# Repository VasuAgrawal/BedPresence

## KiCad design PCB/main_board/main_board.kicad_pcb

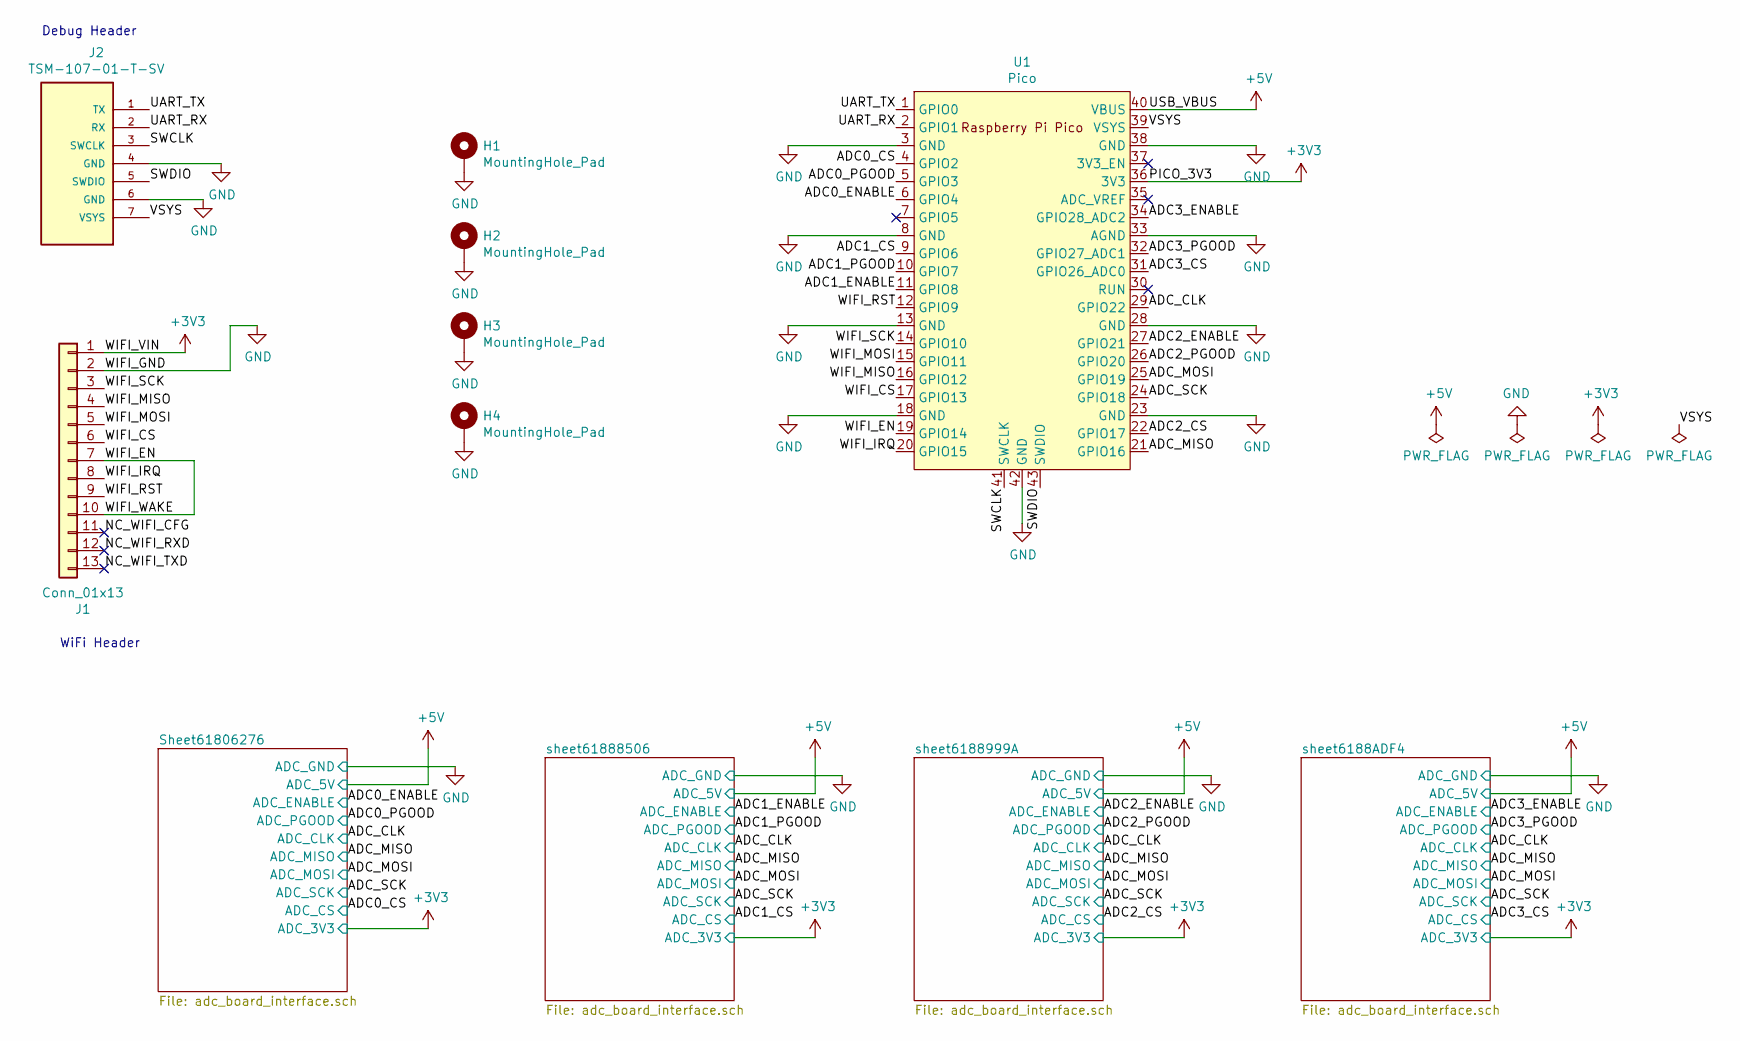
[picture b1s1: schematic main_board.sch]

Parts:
H1, H2, H3, H4: MountingHole_Pad; MountingHole_3.2mm_M3_Pad_Via
J1: Conn_01x13; PinHeader_1x13_P2.54mm_Vertical_SMD_Pin1Left_with_holes
J2: TSM-107-01-T-SV; SAMTEC_TSM-107-01-T-SV
U1: Pico; RPi_Pico_SMD

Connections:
+3V3: J1.1, U1.36 (3V3); also elsewhere on the board
+5V: U1.40 (VBUS); also elsewhere on the board
/ADC0_CS: U1.4 (GPIO2); also elsewhere on the board
/ADC0_ENABLE: U1.6 (GPIO4); also elsewhere on the board
/ADC0_PGOOD: U1.5 (GPIO3); also elsewhere on the board
/ADC1_CS: U1.9 (GPIO6); also elsewhere on the board
/ADC1_ENABLE: U1.11 (GPIO8); also elsewhere on the board
/ADC1_PGOOD: U1.10 (GPIO7); also elsewhere on the board
/ADC2_CS: U1.22 (GPIO17); also elsewhere on the board
/ADC2_ENABLE: U1.27 (GPIO21); also elsewhere on the board
/ADC2_PGOOD: U1.26 (GPIO20); also elsewhere on the board
/ADC3_CS: U1.31 (GPIO26_ADC0); also elsewhere on the board
/ADC3_ENABLE: U1.34 (GPIO28_ADC2); also elsewhere on the board
/ADC3_PGOOD: U1.32 (GPIO27_ADC1); also elsewhere on the board
/ADC_CLK: U1.29 (GPIO22); also elsewhere on the board
/ADC_MISO: U1.21 (GPIO16); also elsewhere on the board
/ADC_MOSI: U1.25 (GPIO19); also elsewhere on the board
/ADC_SCK: U1.24 (GPIO18); also elsewhere on the board
/NC_WIFI_CFG: J1.11
/NC_WIFI_RXD: J1.12
/NC_WIFI_TXD: J1.13
/SWCLK: J2.3 (SWCLK), U1.41 (SWCLK)
/SWDIO: J2.5 (SWDIO), U1.43 (SWDIO)
/UART_RX: J2.2 (RX), U1.2 (GPIO1)
/UART_TX: J2.1 (TX), U1.1 (GPIO0)
/VSYS: J2.7 (VSYS), U1.39 (VSYS)
/WIFI_CS: J1.6, U1.17 (GPIO13)
/WIFI_EN: J1.7, J1.10, U1.19 (GPIO14)
/WIFI_IRQ: J1.8, U1.20 (GPIO15)
/WIFI_MISO: J1.4, U1.16 (GPIO12)
/WIFI_MOSI: J1.5, U1.15 (GPIO11)
/WIFI_RST: J1.9, U1.12 (GPIO9)
/WIFI_SCK: J1.3, U1.14 (GPIO10)
GND: H1.1, H2.1, H3.1, H4.1, J1.2, J2.4 (GND), J2.6 (GND), U1.3 (GND), U1.8 (GND), U1.13 (GND), U1.18 (GND), U1.23 (GND), U1.28 (GND), U1.33 (AGND), U1.38 (GND), U1.42 (GND); also elsewhere on the board

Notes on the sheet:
WiFi Header
Debug Header

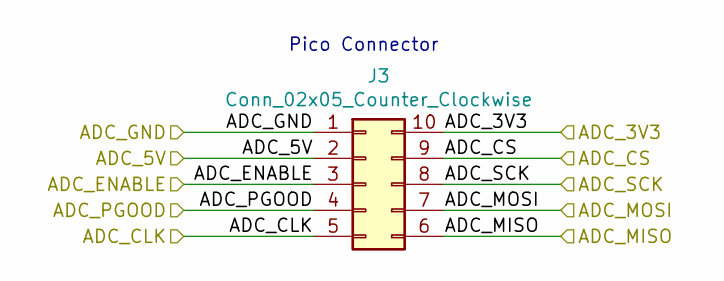
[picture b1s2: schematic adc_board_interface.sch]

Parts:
J3: Conn_02x05_Counter_Clockwise; PinHeader_2x05_P2.54mm_Vertical_SMD

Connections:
+3V3: J3.10; also elsewhere on the board
+5V: J3.2; also elsewhere on the board
/ADC0_CS: J3.9; also elsewhere on the board
/ADC0_ENABLE: J3.3; also elsewhere on the board
/ADC0_PGOOD: J3.4; also elsewhere on the board
/ADC_CLK: J3.5; also elsewhere on the board
/ADC_MISO: J3.6; also elsewhere on the board
/ADC_MOSI: J3.7; also elsewhere on the board
/ADC_SCK: J3.8; also elsewhere on the board
GND: J3.1; also elsewhere on the board

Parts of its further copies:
J4, J5, J6: Conn_02x05_Counter_Clockwise; PinHeader_2x05_P2.54mm_Vertical_SMD

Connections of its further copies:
+3V3: J4.10, J5.10, J6.10; also elsewhere on the board
+5V: J4.2, J5.2, J6.2; also elsewhere on the board
/ADC1_CS: J4.9; also elsewhere on the board
/ADC1_ENABLE: J4.3; also elsewhere on the board
/ADC1_PGOOD: J4.4; also elsewhere on the board
/ADC2_CS: J5.9; also elsewhere on the board
/ADC2_ENABLE: J5.3; also elsewhere on the board
/ADC2_PGOOD: J5.4; also elsewhere on the board
/ADC3_CS: J6.9; also elsewhere on the board
/ADC3_ENABLE: J6.3; also elsewhere on the board
/ADC3_PGOOD: J6.4; also elsewhere on the board
/ADC_CLK: J4.5, J5.5, J6.5; also elsewhere on the board
/ADC_MISO: J4.6, J5.6, J6.6; also elsewhere on the board
/ADC_MOSI: J4.7, J5.7, J6.7; also elsewhere on the board
/ADC_SCK: J4.8, J5.8, J6.8; also elsewhere on the board
GND: J4.1, J5.1, J6.1; also elsewhere on the board

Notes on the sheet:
Pico Connector

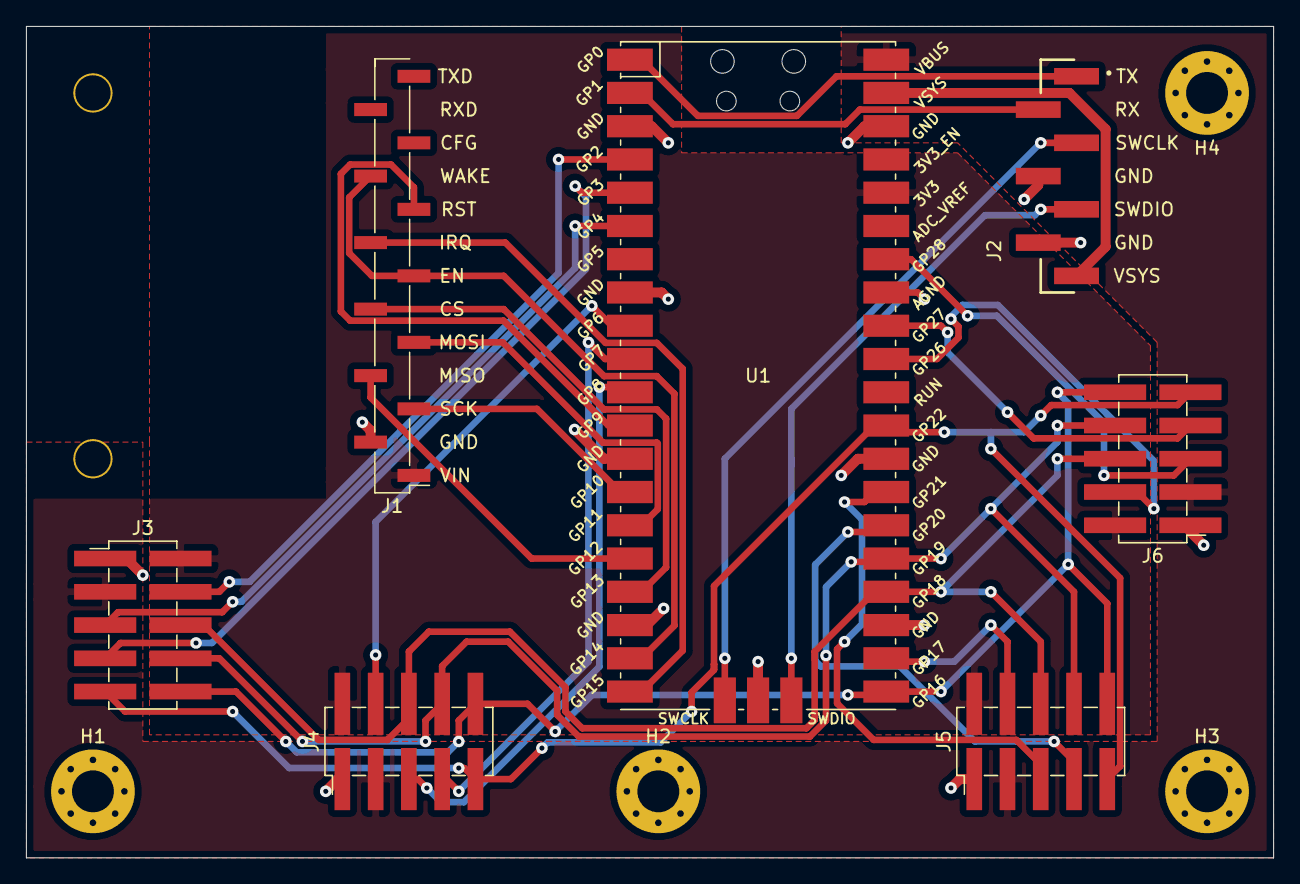
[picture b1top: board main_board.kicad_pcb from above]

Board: 2 copper layers, 95.2 x 63.5 mm, 11 parts (0 on the bottom side), 31 nets.

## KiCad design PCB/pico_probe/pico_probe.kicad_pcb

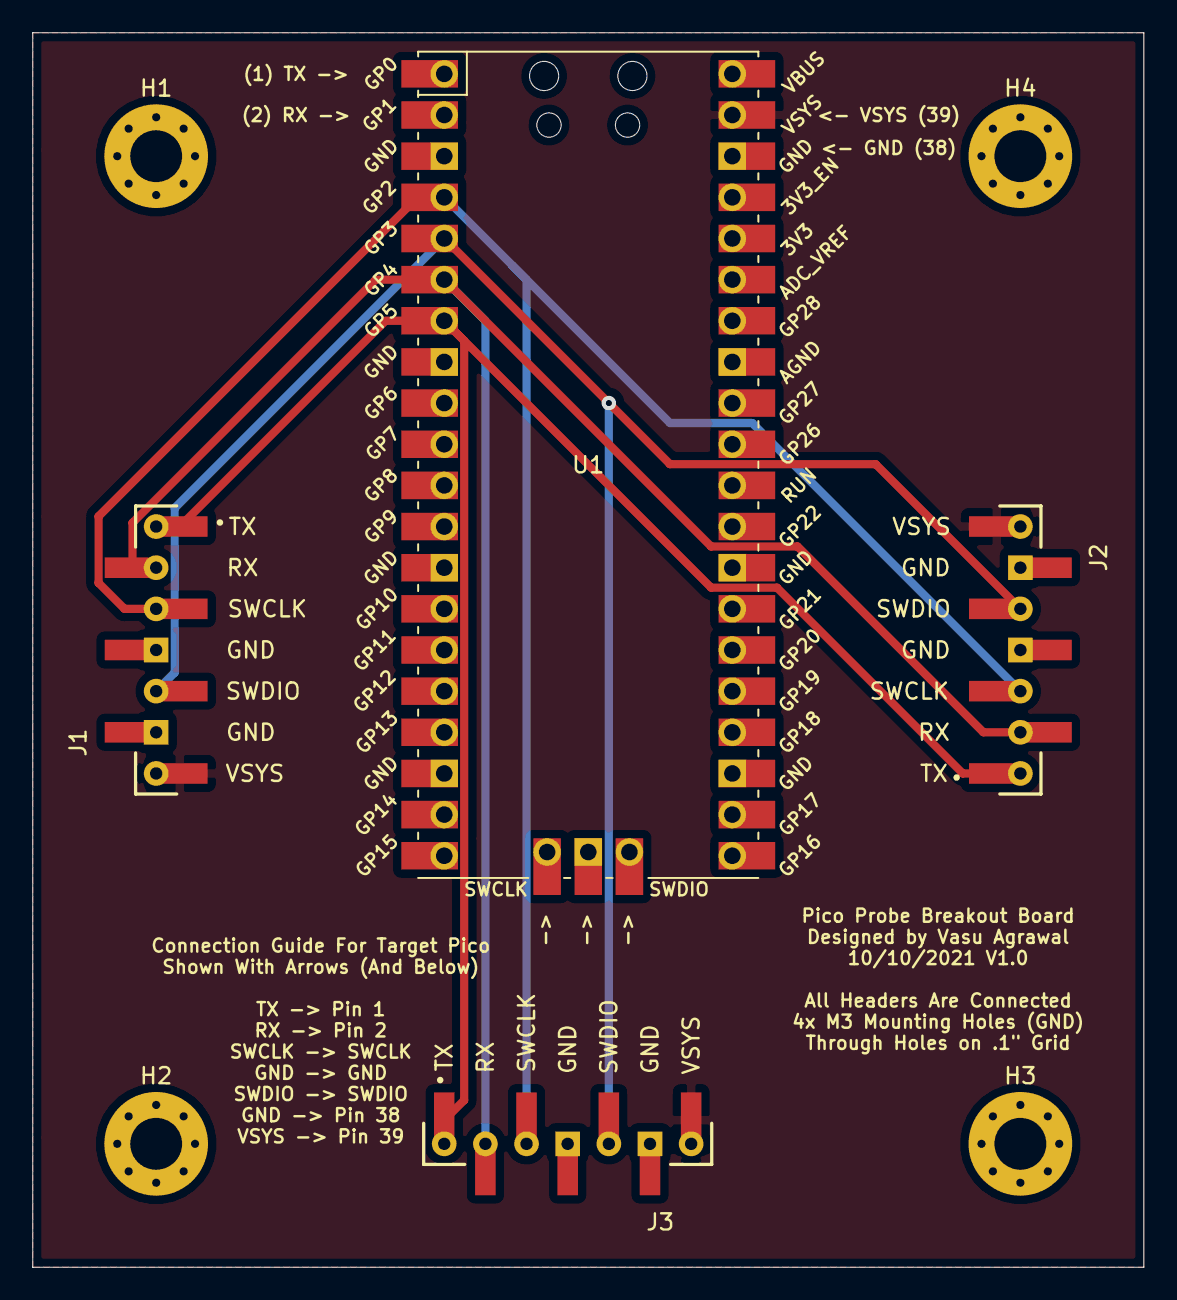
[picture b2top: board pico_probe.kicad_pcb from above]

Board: 2 copper layers, 68.6 x 76.2 mm, 8 parts (0 on the bottom side), 6 nets.

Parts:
H1, H2, H3, H4: MountingHole_Pad; MountingHole_3.2mm_M3_Pad_Via
J1, J2, J3: TSM-107-01-T-SV; SAMTEC_TSM-107-01-T-SV_THRU
U1: Pico; RPi_Pico_SMD_TH

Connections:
/PROBE_UART1_RX: J1.1, J2.1, J3.1, U1.7
/PROBE_UART1_TX: J1.2, J2.2, J3.2, U1.6
/SWCLK: J1.3, J2.3, J3.3, U1.4
/SWDIO: J1.5, J2.5, J3.5, U1.5
/VSYS: J1.7, J2.7, J3.7, U1.39
GND: H1.1, H2.1, H3.1, H4.1, J1.4, J1.6, J2.4, J2.6, J3.4, J3.6, U1.3, U1.8, U1.13, U1.18, U1.23, U1.28, U1.33, U1.38, U1.42

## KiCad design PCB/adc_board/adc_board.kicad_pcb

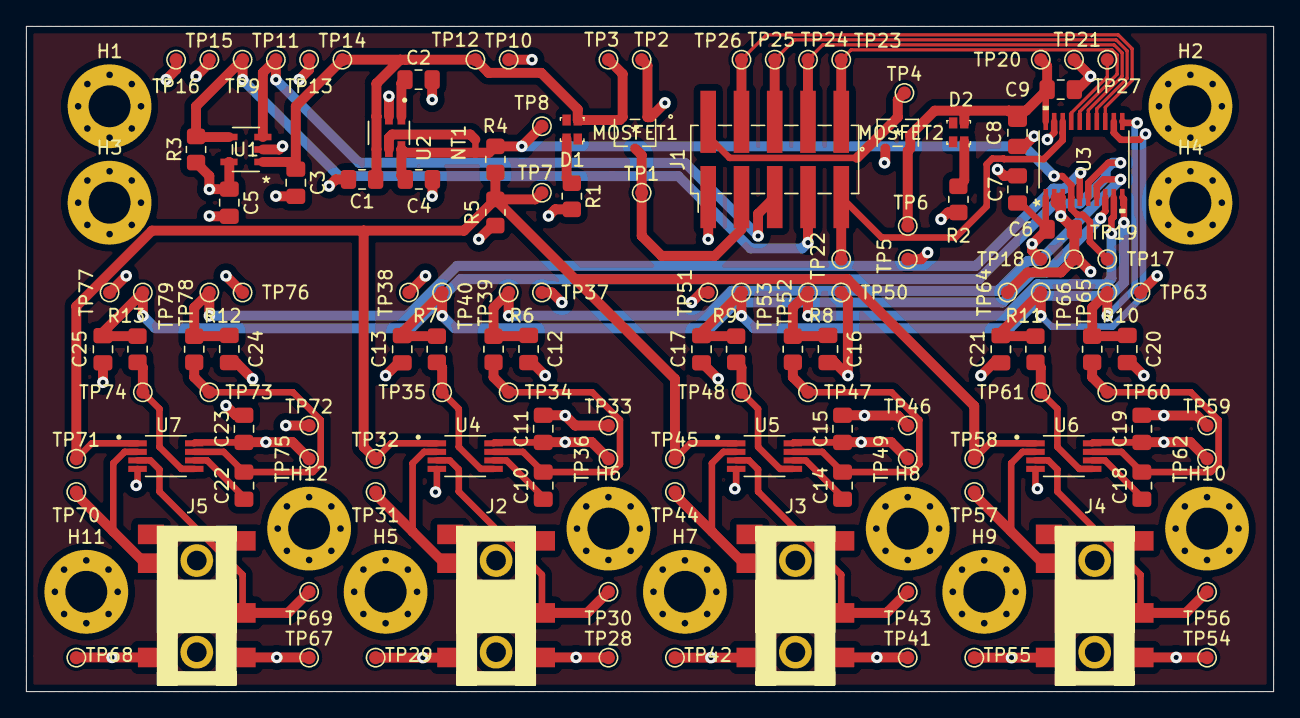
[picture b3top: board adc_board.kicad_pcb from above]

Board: 4 copper layers, 95.2 x 50.8 mm, 146 parts (0 on the bottom side), 48 nets.

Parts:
C1, C2, C4, C6, C9, C11, C12, C13, C15, C16, C17, C19, C20, C21, C23, C24, C25: 0.1uF; C_0805_2012Metric_Pad1.18x1.45mm_HandSolder
C3, C5, C7, C8: 10uF; C_0805_2012Metric_Pad1.18x1.45mm_HandSolder
C10, C14, C18, C22: 10nF; C_0805_2012Metric_Pad1.18x1.45mm_HandSolder
D1, D2: LTST-C19HE1WT; LED_Dual0603
H1, H2, H3, H4, H5, H6, H7, H8, H9, H10, H11, H12: MountingHole; MountingHole_3.2mm_M3_Pad_Via
J1: Conn_02x05_Counter_Clockwise; PinHeader_2x05_P2.54mm_Vertical_SMD
J2, J3, J4, J5: 54-00177
MOSFET1, MOSFET2: SSM3J332R
NT1: Net-Tie_2; NetTie-2_SMD_Pad0.5mm
R1, R2, R6, R7, R8, R9, R10, R11, R12, R13: 100R; R_0805_2012Metric_Pad1.20x1.40mm_HandSolder
R3, R4, R5: 10K 0.5%; R_0805_2012Metric_Pad1.20x1.40mm_HandSolder
TP1, TP4: 3V3; TestPoint_Pad_D1.0mm
TP2, TP5, TP10, TP13, TP16, TP19, TP21, TP29, TP33, TP37, TP38, TP42, TP46, TP50, TP51, TP55, TP59, TP63, TP64, TP68, TP72, TP76, TP77: GND; TestPoint_Pad_D1.0mm
TP3, TP12, TP14: 5V_PROT; TestPoint_Pad_D1.0mm
TP6: 3V3_PROT; TestPoint_Pad_D1.0mm
TP7: 1V65_REF; TestPoint_Pad_D1.0mm
TP8, TP17: 3V3_REF; TestPoint_Pad_D1.0mm
TP9: PGOOD; TestPoint_Pad_D1.0mm
TP11: ENABLE; TestPoint_Pad_D1.0mm
TP15, TP18: AVDD; TestPoint_Pad_D1.0mm
TP20: DVDD; TestPoint_Pad_D1.0mm
TP22: CLK; TestPoint_Pad_D1.0mm
TP23: MISO; TestPoint_Pad_D1.0mm
TP24: MOSI; TestPoint_Pad_D1.0mm
TP25: SCK; TestPoint_Pad_D1.0mm
TP26: CS; TestPoint_Pad_D1.0mm
TP27: IRQ; TestPoint_Pad_D1.0mm
TP28, TP36, TP41, TP49, TP54, TP62, TP67, TP75: VDD; TestPoint_Pad_D1.0mm
TP30, TP43, TP56, TP69: BR+; TestPoint_Pad_D1.0mm
TP31, TP44, TP57, TP70: BR-; TestPoint_Pad_D1.0mm
TP32, TP45, TP58, TP71: 1V65; TestPoint_Pad_D1.0mm
TP34, TP47, TP60, TP73: AMP+; TestPoint_Pad_D1.0mm
TP35, TP48, TP61, TP74: AMP-; TestPoint_Pad_D1.0mm
TP39, TP52, TP65, TP78: DIFF+; TestPoint_Pad_D1.0mm
TP40, TP53, TP66, TP79: DIFF-; TestPoint_Pad_D1.0mm
U1: MCP1755T-3302E_OT; MCP1755T-3302E&slash_OT
U2: MAX6070BAUT33T; SOT95P280X145-6N
U3: MCP3564-E_ST; MCP3564-E&slash_ST
U4, U5, U6, U7: MAX4209HAUA; SOP65P490X110-8N

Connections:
+3V3: J1.10, MOSFET2.3, TP4.1
+5V: J1.2, MOSFET1.3, TP1.1
/1V65_REF: R4.2, R5.1, TP7.1, TP32.1, TP45.1, TP58.1, TP71.1, U4.1, U5.1, U6.1, U7.1
/3V3_PROT: C8.1, C9.1, D2.4, MOSFET2.2, TP6.1, TP20.1, U3.20
/3V3_REF_FILTER: C2.1, U2.1
/3V3_REF_OUT: C4.1, NT1.2, R4.1, TP8.1, TP17.1, U2.6, U3.4
/3V3_REF_OUTS: NT1.1, U2.5
/3V3_REF_VIN: C1.1, C3.1, D1.4, MOSFET1.2, TP3.1, TP12.1, TP14.1, U1.1, U2.3, U2.4
/ADC_AVDD: C5.1, C6.1, C7.1, C11.1, C15.1, C19.1, C23.1, J2.1, J3.1, J4.1, J5.1, R3.1, TP15.1, TP18.1, TP28.1, TP36.1, TP41.1, TP49.1, TP54.1, TP62.1, TP67.1, TP75.1, U1.5, U3.1, U4.8, U5.8, U6.8, U7.8
/ADC_CLK: J1.5, TP22.1, U3.18
/ADC_IRQ: TP27.1, U3.17
/CS: J1.9, TP26.1, U3.13
/ENABLE: J1.3, TP11.1, U1.3
/MISO: J1.6, TP23.1, U3.16
/MOSI: J1.7, TP24.1, U3.15
/PGOOD: J1.4, R3.2, TP9.1, U1.4
/SCK: J1.8, TP25.1, U3.14
/Sheet61550FD4/ADC_CH0: C24.1, R12.2, TP78.1, U3.5
/Sheet61550FD4/ADC_CH1: C25.1, R13.2, TP79.1, U3.6
/Sheet61550FD4/ADC_CH2: C12.1, R6.2, TP39.1, U3.7
/Sheet61550FD4/ADC_CH3: C13.1, R7.2, TP40.1, U3.8
/Sheet61550FD4/ADC_CH4: C16.1, R8.2, TP52.1, U3.9
/Sheet61550FD4/ADC_CH5: C17.1, R9.2, TP53.1, U3.10
/Sheet61550FD4/ADC_CH6: C20.1, R10.2, TP65.1, U3.11
/Sheet61550FD4/ADC_CH7: C21.1, R11.2, TP66.1, U3.12
/Sheet61550FD4/Bridge0/BRIDGE+: J5.3, TP69.1, U7.3
/Sheet61550FD4/Bridge0/BRIDGE-: J5.4, TP70.1, U7.2
/Sheet61550FD4/Bridge0/INST_AMP+: C22.1, R12.1, TP73.1, U7.7
/Sheet61550FD4/Bridge0/INST_AMP-: R13.1, TP74.1, U7.5
/Sheet61550FD4/Bridge1/BRIDGE+: J2.3, TP30.1, U4.3
/Sheet61550FD4/Bridge1/BRIDGE-: J2.4, TP31.1, U4.2
/Sheet61550FD4/Bridge1/INST_AMP+: C10.1, R6.1, TP34.1, U4.7
/Sheet61550FD4/Bridge1/INST_AMP-: R7.1, TP35.1, U4.5
/Sheet61550FD4/Bridge2/BRIDGE+: J3.3, TP43.1, U5.3
/Sheet61550FD4/Bridge2/BRIDGE-: J3.4, TP44.1, U5.2
/Sheet61550FD4/Bridge2/INST_AMP+: C14.1, R8.1, TP47.1, U5.7
/Sheet61550FD4/Bridge2/INST_AMP-: R9.1, TP48.1, U5.5
/Sheet61550FD4/Bridge3/BRIDGE+: J4.3, TP56.1, U6.3
/Sheet61550FD4/Bridge3/BRIDGE-: J4.4, TP57.1, U6.2
/Sheet61550FD4/Bridge3/INST_AMP+: C18.1, R10.1, TP60.1, U6.7
/Sheet61550FD4/Bridge3/INST_AMP-: R11.1, TP61.1, U6.5
GND: C1.2, C2.2, C3.2, C4.2, C5.2, C6.2, C7.2, C8.2, C9.2, C11.2, C12.2, C13.2, C15.2, C16.2, C17.2, C19.2, C20.2, C21.2, C23.2, C24.2, C25.2, H1.1, H2.1, H3.1, H4.1, H5.1, H6.1, H7.1, H8.1, H9.1, H10.1, H11.1, H12.1, J1.1, J2.2, J3.2, J4.2, J5.2, MOSFET1.1, MOSFET2.1, R1.2, R2.2, R5.2, TP2.1, TP5.1, TP10.1, TP13.1, TP16.1, TP19.1, TP21.1, TP29.1, TP33.1, TP37.1, TP38.1, TP42.1, TP46.1, TP50.1, TP51.1, TP55.1, TP59.1, TP63.1, TP64.1, TP68.1, TP72.1, TP76.1, TP77.1, U1.2, U2.2, U3.2, U3.3, U3.19, U4.4, U5.4, U6.4, U7.4
unnamed: C10.2, U4.6
unnamed: C14.2, U5.6
unnamed: C18.2, U6.6
unnamed: C22.2, U7.6
unnamed: D1.2, R1.1
unnamed: D2.1, R2.1

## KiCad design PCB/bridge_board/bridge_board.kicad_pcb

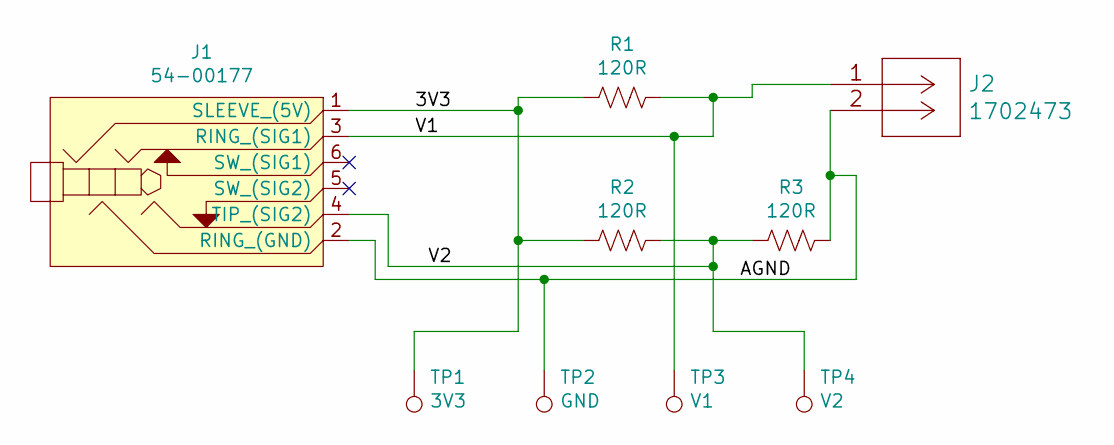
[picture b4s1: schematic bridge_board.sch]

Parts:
J1: 54-00177
J2: 1702473
R1, R2, R3: 120R; R_0805_2012Metric_Pad1.20x1.40mm_HandSolder
TP1: 3V3; TestPoint_Pad_D1.5mm
TP2: GND; TestPoint_Pad_D1.5mm
TP3: V1; TestPoint_Pad_D1.5mm
TP4: V2; TestPoint_Pad_D1.5mm

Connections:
/3V3: J1.1 (SLEEVE_(5V)), R1.2, R2.1, TP1.1
/AGND: J1.2 (RING_(GND)), J2.2, R3.2, TP2.1
/V1: J1.3 (RING_(SIG1)), J2.1, R1.1, TP3.1
/V2: J1.4 (TIP_(SIG2)), R2.2, R3.1, TP4.1

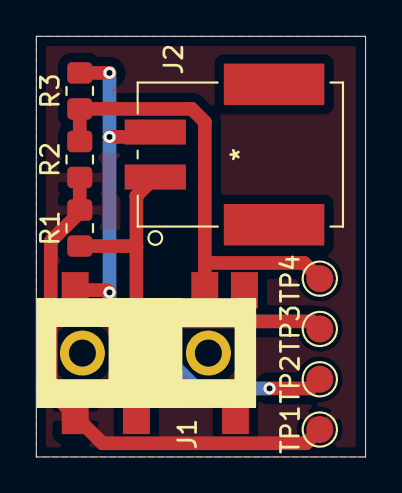
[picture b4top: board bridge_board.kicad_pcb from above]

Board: 4 copper layers, 18.3 x 23.4 mm, 9 parts (0 on the bottom side), 4 nets.

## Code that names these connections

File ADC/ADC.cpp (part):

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#define PIN_MOSI 19
#define PIN_CLK 22

#define PIN_ADC0_ENABLE 4
#define PIN_ADC0_PGOOD 3
#define PIN_ADC0_CS 2

#define PIN_ADC1_ENABLE 8
#define PIN_ADC1_PGOOD 7
#define PIN_ADC1_CS 6

#define PIN_ADC2_ENABLE 21
#define PIN_ADC2_PGOOD 20
#define PIN_ADC2_CS 17

#define PIN_ADC3_ENABLE 28
#define PIN_ADC3_PGOOD 27
#define PIN_ADC3_CS 26

#define PIN_IRQ 6

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  const uint32_t f_clk_sys = frequency_count_khz(CLOCKS_FC0_SRC_VALUE_CLK_SYS);
  printf("clk_sys = %dkHz\n", f_clk_sys);

  gpio_set_function(PIN_CLK, GPIO_FUNC_PWM);  // GPIO22 is on physical pin 29

  const auto slice_num = pwm_gpio_to_slice_num(PIN_CLK);
  const auto channel_num = pwm_gpio_to_channel(PIN_CLK);
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
  configureStdio();

  gpio_init(PIN_ADC0_ENABLE);
  gpio_init(PIN_ADC1_ENABLE);
  gpio_init(PIN_ADC2_ENABLE);
  gpio_init(PIN_ADC3_ENABLE);

  gpio_set_dir(PIN_ADC0_ENABLE, GPIO_OUT);
  gpio_set_dir(PIN_ADC1_ENABLE, GPIO_OUT);
  gpio_set_dir(PIN_ADC2_ENABLE, GPIO_OUT);
  gpio_set_dir(PIN_ADC3_ENABLE, GPIO_OUT);

  gpio_put(PIN_ADC0_ENABLE, 1);
  gpio_put(PIN_ADC1_ENABLE, 1);
  gpio_put(PIN_ADC2_ENABLE, 1);
  gpio_put(PIN_ADC3_ENABLE, 1);

  gpio_set_dir(PIN_ADC0_PGOOD, GPIO_IN);
  gpio_set_dir(PIN_ADC1_PGOOD, GPIO_IN);
  gpio_set_dir(PIN_ADC2_PGOOD, GPIO_IN);
  gpio_set_dir(PIN_ADC3_PGOOD, GPIO_IN);

  // Check that we have pgood
  // while (!gpio_get(PIN_ADC0_PGOOD)) {}
  // printf("Have pgood on ADC0");
  //
  // while (!gpio_get(PIN_ADC1_PGOOD)) {}
  // printf("Have pgood on ADC1");

  while (!gpio_get(PIN_ADC2_PGOOD)) {
  }
  printf("Have pgood on ADC2\n");

  // while (!gpio_get(PIN_ADC3_PGOOD)) {}
  // printf("Have pgood on ADC3");

  configureSpi(PIN_ADC2_CS);
  // validateDefaultRegisterMap();

  auto adc_config = configureAdc(PIN_ADC2_CS);

  // Make sure to start the external clock only after we've told the ADC to
  // expect the external clock.
  configurePwm(5e6);

  // Start reading data!
  startAdc(PIN_ADC2_CS, adc_config);

  readAdc(PIN_ADC2_CS);

  return 0;
}
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
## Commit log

2021-07-02 Initial commit, host build working
    Will take the next diff to clean up the code and use a struct for better
    register map naming.
2021-07-02 Add build script
2021-07-05 Complete initial pass at configuration
    Finally got all the configuration registers added, with the notable
    exception of the SCAN register. Time to move on to configuring the clock
    before I actually turn this thing on.
2021-07-05 Read from ADC
    Gave up on interrupts temporarily. For now, we'll just stick to polling
    on the GPIO pin, since the pico doesn't actually have to do anything
    else.
2021-08-05 Determine voltage reading
    I added some code to print out the voltage reading. It looks like the
    voltage isn't quite what I expect it to be - I'm not sure whether this
    is because the voltage reference isn't as stable as I want it to be, or
    because there's noise, or something else. I'm hoping some of the noise
    issues go away when I make a PCB (since I'll have decoupling caps
    everywhere, and the wires won't all be acting as gigantic antennas).
2021-08-16 First time putting everything together
    I finally figured out how negative inputs work.
    You can feed two ground-referenced signals to the two inputs, and then
    the ADC will subtract the two and give you the converted difference,
    scaled to the +/- ADC reference value. So, you could have output values
    from the range -V_ref to +V_ref.
    I feed the reference voltage from the amplifier as the Vin_minus, and
2021-08-16 Move git to parent directory
2021-08-31 Adding bridge_board v1 PCB
2021-09-15 Added mostly-complete version of main board
2021-10-10 ADC board schematic done
2021-10-10 Finished layout for adc board
2021-10-10 reverted mounting hole mistake
2021-10-10 whatever the latest changes were
2021-10-11 Added pico probe board
2021-10-16 Adding gerbers, and updated version of main board
2021-10-16 Add BOM files
2022-02-28 Update ADC code for real board

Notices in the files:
parts and their libraries:
Copyright 2021 Accelerated Designs. All rights reserved.
